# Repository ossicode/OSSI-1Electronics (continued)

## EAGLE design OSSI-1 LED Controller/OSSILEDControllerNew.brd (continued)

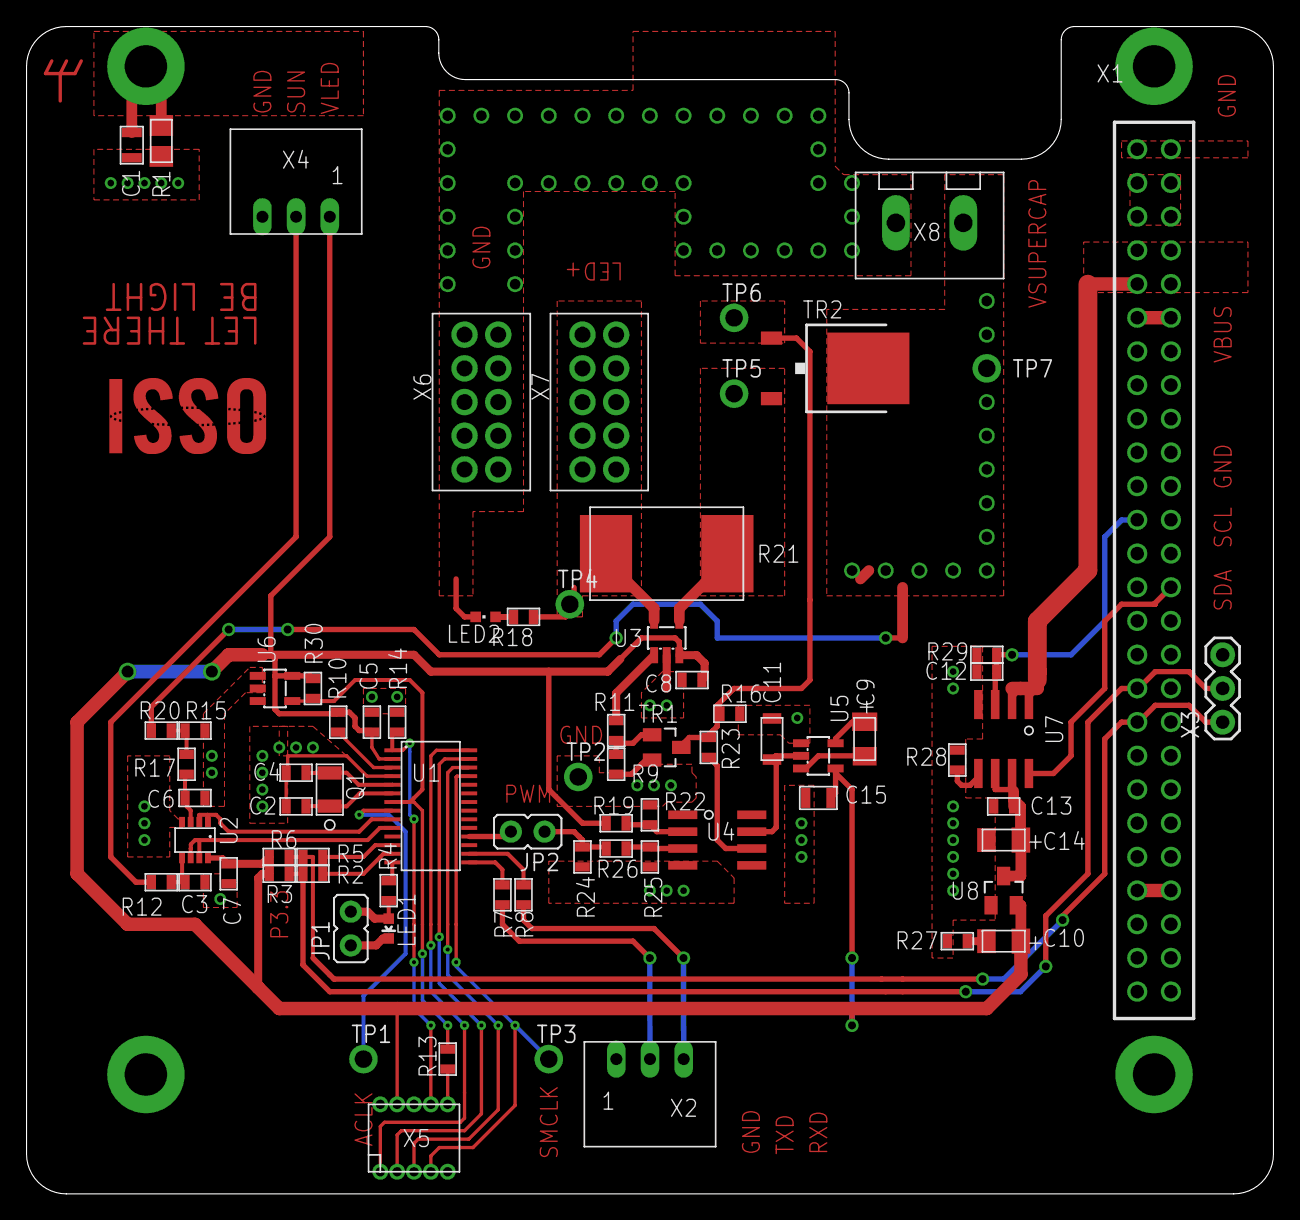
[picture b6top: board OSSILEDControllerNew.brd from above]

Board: 2 copper layers, 94.0 x 88.0 mm, 80 parts (0 on the bottom side), 54 nets.

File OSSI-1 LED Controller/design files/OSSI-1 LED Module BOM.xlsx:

Part | Value | Package | Description | Note | Manufacturer | Part Num | Order
C1 | DNP | C0805(2012)
H1 | MOUNT-PAD-ROUND3.2 | 3.2-PAD-ROUND
H2 | MOUNT-PAD-ROUND3.2 | 3.2-PAD-ROUND
H3 | MOUNT-PAD-ROUND3.2 | 3.2-PAD-ROUND
H4 | MOUNT-PAD-ROUND3.2 | 3.2-PAD-ROUND
R1 | DNP | WSL1206
X1 | ESQ-126-38-G-D | ESQ-126-XX-X-D | Samtec ESQ-126-XX-G-D Elevated Sockets Seires | Used by many satellites | Samtec | ESQ-126-38-G-D | Samtec.com
C2 | 12.5pF | C0603(1608)
C3 | 100nF | C0603(1608)
C4 | 12.5pF | C0603(1608)
C5 | 100nF | C0603(1608)
C6 | 100nF | C0603(1608)
C7 | 100nF | C0603(1608)
C8 | 100nF | C0603(1608)
C9 | 10uF, LDO Tantal 16V | C1206(3216)-A | TAJA105M020RNJ | Tantal Capacitor for LDO | Vishay Sprague | TR3A106K016C1700 | Digikey.com
C10 | 10uF, LDO Tantal 16V | C1206(3216)-A | TAJA105M020RNJ | Tantal Capacitor for LDO | Vishay Sprague | TR3A106K016C1700 | Digikey.com
C11 | 4.7uF, 1206 Cap | C1206-GCM31
C12 | 1uF | C0603(1608)
C13 | 100nF | C0603(1608)
C14 | 10uF, LDO Tantal 16V | C1206(3216)-A | TAJA105M020RNJ | Tantal Capacitor for LDO | Vishay Sprague | TR3A106K016C1700 | Digikey.com
C15 | 1uF 0805 | C0805(2012) |  | 35V, X7R | Murata | GCM21BR7YA105KA55L | Digikey.com
JP1 |  | JP1 | JUMPER
JP2 |  | JP1 | JUMPER
LED1 |  | LED-0603 | LEDs
LED2 |  | CHIPLED_0603 | LED
Q1 | NX-3215 | NX-3215 | NDK 32.768 kHz SMD Crystal | Automotive Grade | NDK | NX3215SA-32.768K-STD-MUS-2 | Digikey.com
R2 | 250 | R0603(1608)
R3 | 10k | R0603(1608)
R4 | 1k | R0603(1608)
R5 | 250 | R0603(1608)
R6 | 10k | R0603(1608)
R7 | 4.7k | R0603(1608)
R8 | 4.7k | R0603(1608)
R9 | 3k | R0603(1608)
R10 | 1k | R0603(1608)
R11 | 5.1k | R0603(1608)
R12 | 1k | R0603(1608)
R13 | 4.7k | R0603(1608)
R14 | 47k | R0603(1608)
R15 | 100k | R0603(1608)
R16 | DNP | R0603(1608)
R17 | 1k | R0603(1608)
R18 | 1.5k | R0603(1608)
R19 | 2.4k | R0603(1608)
R20 | 100k | R0603(1608)
R21 | 0.005, 2W RSENSE | R4527(12070) |  | High Power (2W) 1% Current Sense Resistor | Vishay Dale | WSR25L000FEA | element14.com
R22 | 1.1k | R0603(1608)
R23 | 1k | R0603(1608)
R24 | 100k | R0603(1608)
R25 | DNP | R0603(1608)
R26 | 1.5k | R0603(1608)
R27 | 0 | R0603(1608)
R28 | TBD | R0603(1608)
R29 | 100k | R0603(1608)
R30 | 100k | R0603(1608)
TP1 | TP | TP-13
TP2 | TP | TP-13
TP3 | TP | TP-13
TP4 | TP | TP-13
TP5 | TP | TP-13
TP6 | TP | TP-13
TP7 | TP | TP-13
TR1 | FDV301N | SOT23 | FDV301N Digital N channel - FET | Used sucessfully by swisscube | Fairchild Semiconductor | FDV301N | Digikey.com
TR2 | FDD8896 | TO252 | FDD8896 | 30V 94A N-Ch Mosfet for 9A pulse LED driving | Fairchild Semiconductor | FDD8896 | Digikey.com
U$ | OSSILOGORECT | OSSILOGORECT1005
U1 | MSP430F2132 | PW28 | *** MSP430F21x2 *** PW28 | high current rating | Texas Instruements | MSP430F2132TPWR | Digikey.com
U2 | OPA2347 | SOT23-8DCN | OPA2347 | op-amp | Texas Instruements | OPA2347EA/250 | Digikey.com
U3 | MAX4376 | SOT23-5DBV |  | Current Sensor, Gain = 50 | Maxim IC | MAX4376FAUK+T | Digikey.com
U4 | LM7321 | SO8 | LM7321 | op-amp used as mosfet driver | Texas Instruements | LM7321MA/NOPB | element14.com
U5 | MAX1682 | SOT23-5DBV | MAX1682EUK+T Charge Pump | Charge pump for lm7321 power | Maxim IC | MAX1682EUK+T | Digikey.com
U6 | TPS3838 | SOT23-5DBV | TPS3838 | IC Supervisor for relaible power-on | Texas Instruements | TPS3838K33QDBVRQ1 | Digikey.com
U7 | MAX890L | SO8 | MAX 890L | Current Limiter for SEU / SEL | Maxim IC | MAX890LESA+ | Digikey.com
U8 | MCP1700_SOT23 | SOT23 | MCP1700 LDO from Microchips | LDO used successfully by cubesats / External Capacitor is not that important co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 | Microchip | MCP1700T-3302E/TT | Digikey.com
X2 | 5268-03 | 5268-03
X3 |  | 1X03 | Header 3
X4 | 5268-03 | 5268-03
X5 | JTAG10PINMINI-H | M50-3200545 |  | Mini right angle 10-pin JTAG for MSP430 | Harwin Inc | M50-3200545 | Digikey.com
X6 | ICCON_POWERCON | ICCON6643220-1 |  | 35A rated power connector for led power | TE Connectivity | 6643220-1
X7 | ICCON_POWERCON | ICCON6643220-1 |  | 35A rated power connector for led power | TE Connectivity | 6643220-1
X8 | WEIDMULLER | WEIDMULLER1760490000 |  | 15A rated connector for led connection | Weidmuller | 1760490000
Unless noted othersie,_x000a_- Capacitors: GCM series from Murata / CGA series 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

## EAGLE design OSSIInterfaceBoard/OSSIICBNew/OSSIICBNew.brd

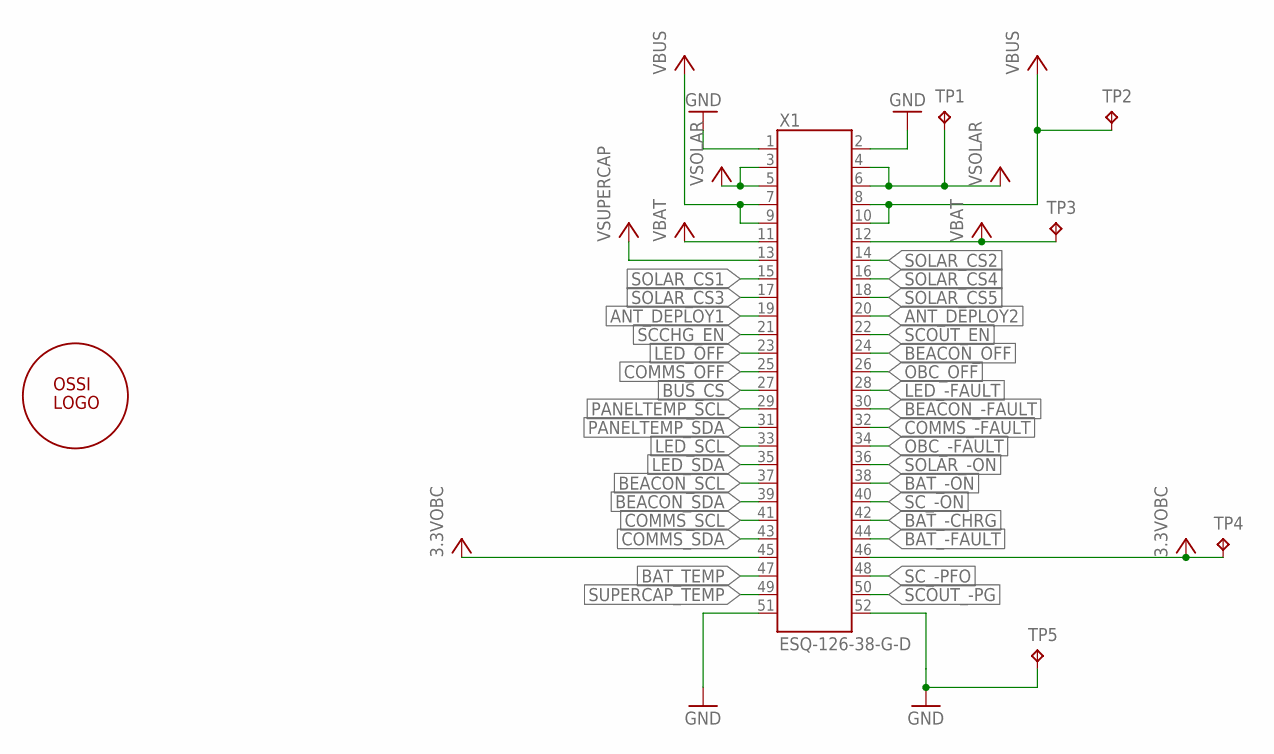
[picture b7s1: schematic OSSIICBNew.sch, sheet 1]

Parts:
TP1, TP2, TP3, TP4, TP5: TP; TP-13
U$1: OSSILOGO-10; OSSILOGO1010
X1: ESQ-126-38-G-D; ESQ-126-XX-X-D

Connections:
3.3VOBC: TP4.TP, X1.45, X1.46; also elsewhere on the board
ANT_DEPLOY1: X1.19
ANT_DEPLOY2: X1.20
BAT_-CHRG: X1.42
BAT_-FAULT: X1.44
BAT_-ON: X1.38
BAT_TEMP: X1.47
BEACON_-FAULT: X1.30
BEACON_OFF: X1.24
BEACON_SCL: X1.37
BEACON_SDA: X1.39
BUS_CS: X1.27
COMMS_-FAULT: X1.32
COMMS_OFF: X1.25
COMMS_SCL: X1.41
COMMS_SDA: X1.43
GND: TP5.TP, X1.1, X1.2, X1.51, X1.52; also elsewhere on the board
LED_-FAULT: X1.28
LED_OFF: X1.23
LED_SCL: X1.33
LED_SDA: X1.35
OBC_-FAULT: X1.34
OBC_OFF: X1.26
PANELTEMP_SCL: X1.29; also elsewhere on the board
PANELTEMP_SDA: X1.31; also elsewhere on the board
SCCHG_EN: X1.21
SCOUT_-PG: X1.50
SCOUT_EN: X1.22
SC_-ON: X1.40
SC_-PFO: X1.48
SOLAR_-ON: X1.36
SOLAR_CS1: X1.15; also elsewhere on the board
SOLAR_CS2: X1.14; also elsewhere on the board
SOLAR_CS3: X1.17; also elsewhere on the board
SOLAR_CS4: X1.16; also elsewhere on the board
SOLAR_CS5: X1.18; also elsewhere on the board
SUPERCAP_TEMP: X1.49
VBAT: TP3.TP, X1.11, X1.12
VBUS: TP2.TP, X1.7, X1.8, X1.9, X1.10
VSOLAR: TP1.TP, X1.3, X1.4, X1.5, X1.6; also elsewhere on the board
VSUPERCAP: X1.13

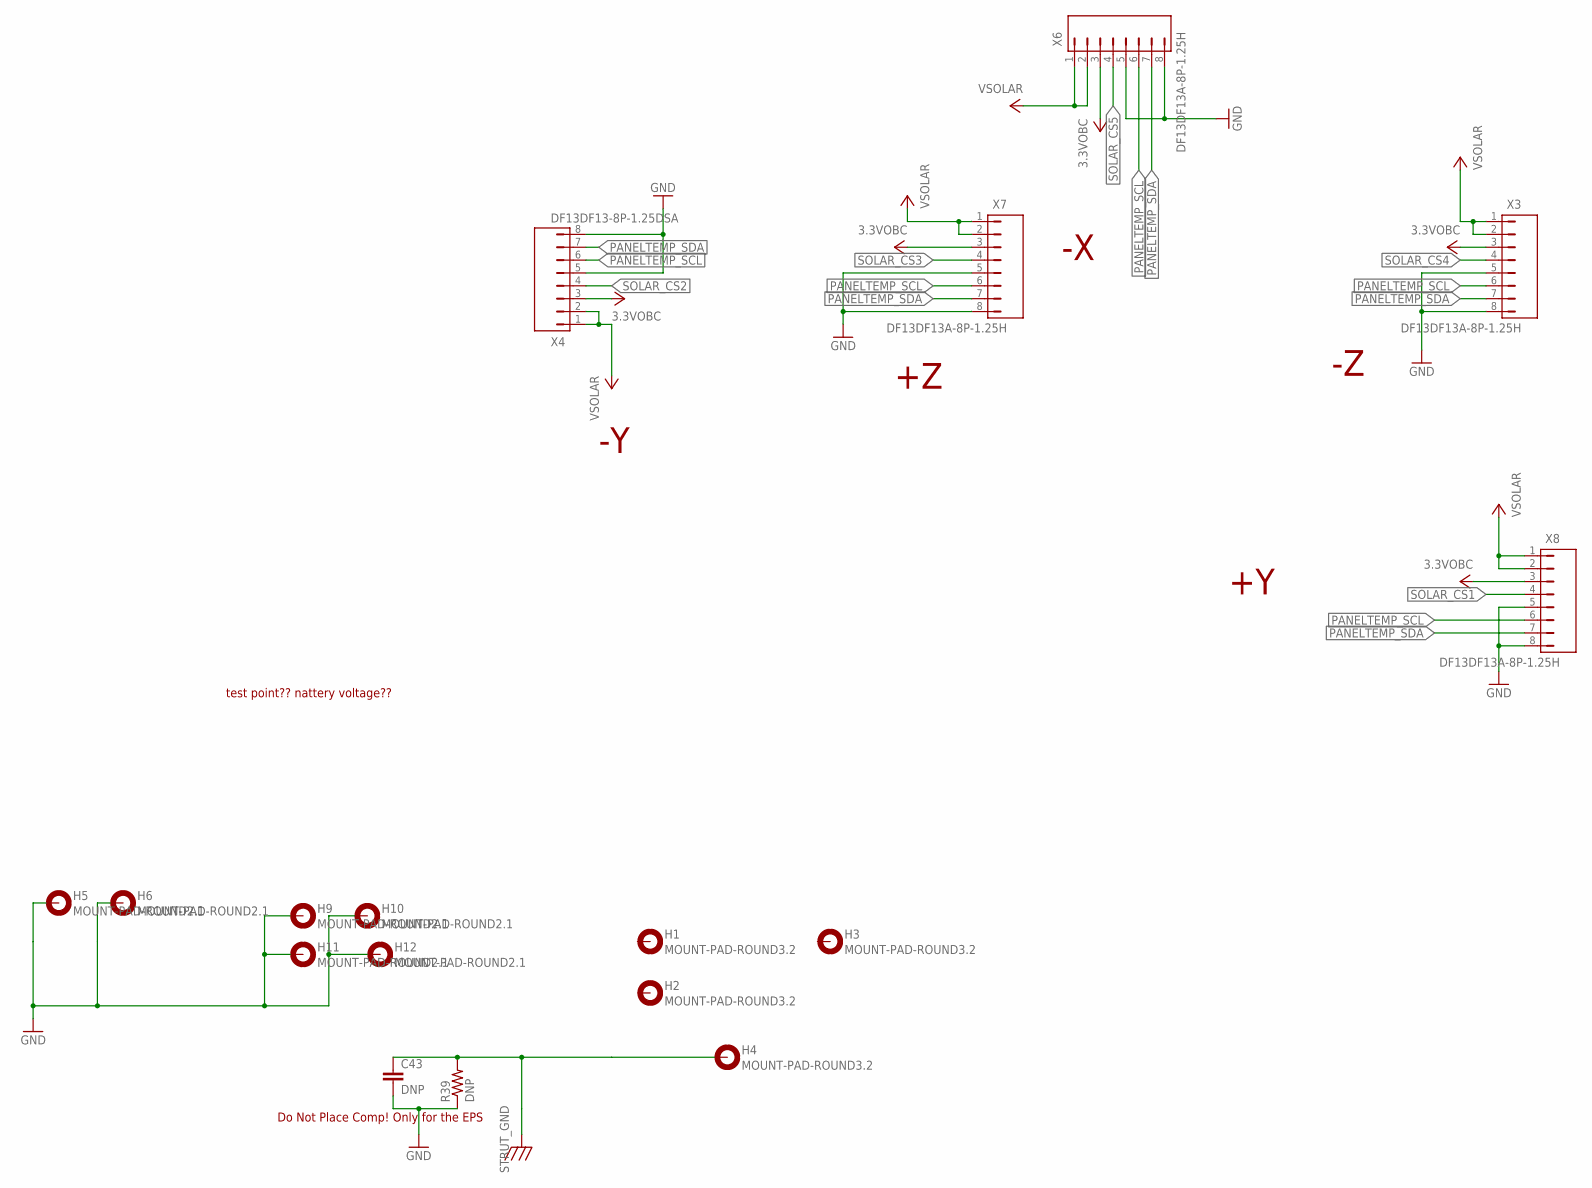
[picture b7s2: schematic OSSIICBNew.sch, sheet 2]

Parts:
C43: DNP; C0805(2012)
H1, H2, H3, H4: MOUNT-PAD-ROUND3.2; 3.2-PAD-ROUND
H5, H6, H9, H10, H11, H12: MOUNT-PAD-ROUND2.1; 2.1-PAD-ROUND
R39: DNP; WSL1206
X3, X6, X7, X8: DF13DF13A-8P-1.25H; DF13A-8P
X4: DF13DF13-8P-1.25DSA; DF13-8P-1.25DSA

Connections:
3.3VOBC: X3.3, X4.3, X6.3, X7.3, X8.3; also elsewhere on the board
GND: C43.2, H5.B3,2, H6.B3,2, H9.B3,2, H10.B3,2, H11.B3,2, H12.B3,2, R39.P$1 (1), X3.5, X3.8, X4.5, X4.8, X6.5, X6.8, X7.5, X7.8, X8.5, X8.8; also elsewhere on the board
PANELTEMP_SCL: X3.6, X4.6, X6.6, X7.6, X8.6; also elsewhere on the board
PANELTEMP_SDA: X3.7, X4.7, X6.7, X7.7, X8.7; also elsewhere on the board
SOLAR_CS1: X8.4; also elsewhere on the board
SOLAR_CS2: X4.4; also elsewhere on the board
SOLAR_CS3: X7.4; also elsewhere on the board
SOLAR_CS4: X3.4; also elsewhere on the board
SOLAR_CS5: X6.4; also elsewhere on the board
STRUT_GND: C43.1, H4.B3,2, R39.P$2 (2)
VSOLAR: X3.1, X3.2, X4.1, X4.2, X6.1, X6.2, X7.1, X7.2, X8.1, X8.2; also elsewhere on the board

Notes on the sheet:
test point?? nattery voltage??
Do Not Place Comp! Only for the EPS

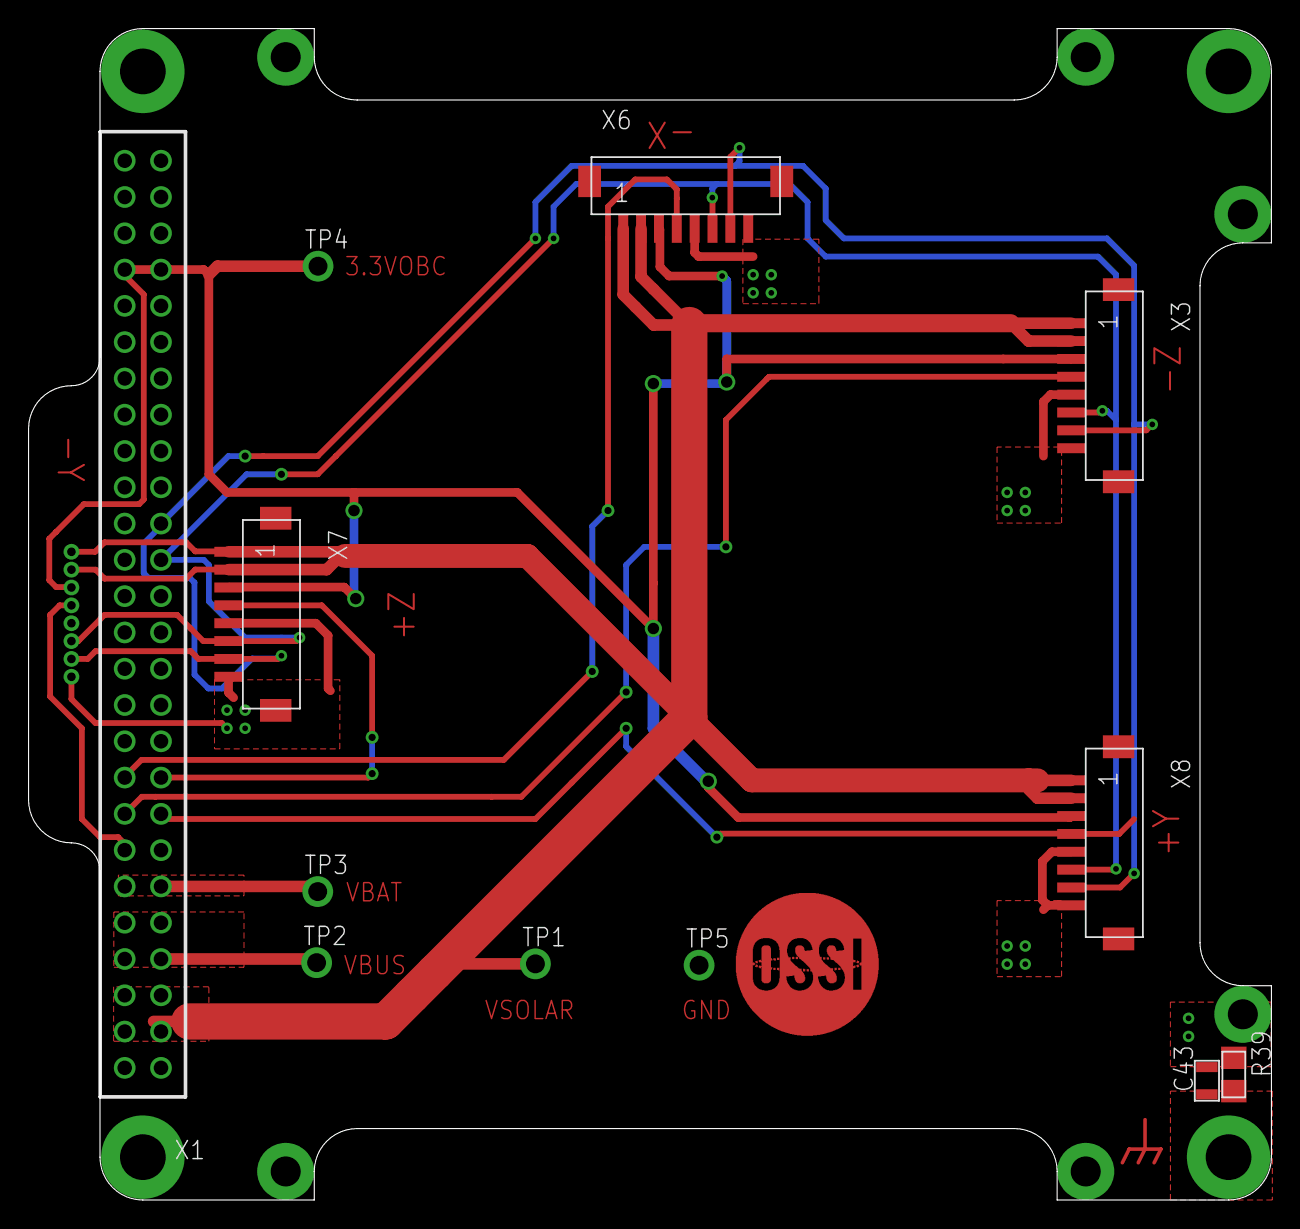
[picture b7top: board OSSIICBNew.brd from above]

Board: 2 copper layers, 87.0 x 82.0 mm, 24 parts (1 on the bottom side), 13 nets.

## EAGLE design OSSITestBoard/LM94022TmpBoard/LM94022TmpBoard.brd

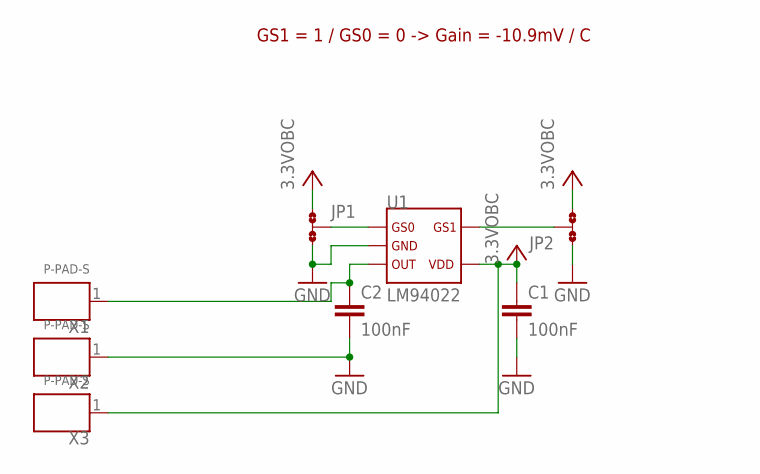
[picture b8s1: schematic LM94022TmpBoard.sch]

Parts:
C1, C2: 100nF; C0603(1608)
JP1, JP2: JP2; JP2SMD0603
U1: LM94022; SC70-5
X1, X2, X3: P-PAD-S

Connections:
3.3VOBC: C1.1, JP1.1, JP2.3, U1.P$4, X3.1
GND: C1.2, C2.2, JP1.3, JP2.1, U1.P$2, X2.1
unnamed: JP1.2, U1.P$1
unnamed: JP2.2, U1.P$5
unnamed: C2.1, U1.P$3, X1.1

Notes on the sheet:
GS1 = 1 / GS0 = 0 -> Gain = -10.9mV / C

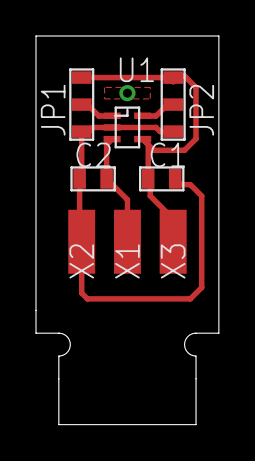
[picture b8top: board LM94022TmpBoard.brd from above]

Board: 2 copper layers, 10.2 x 21.6 mm, 8 parts (0 on the bottom side), 5 nets.

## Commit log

2012-10-20 Readme added
2012-10-20 combining all OSSI-1 electronics related repositories
2012-12-05 LFCSP_VD package for ADL5530 updated
2012-12-05 ADF7012 based OSSI-1 New Beacon Board project created
2012-12-06 MSP430F2132 added / New Beacon Modified
2012-12-06 OSSI New Beacon Board Circuit 90% done
2012-12-06 New Beacon board updating
2012-12-07 CX5032 19.2MHz crystal added to library
2012-12-07 OSSI New Beacon Almost done
2012-12-10 OSSI New Beacon layout done
2012-12-10 I2C Testboard gerber done / New Beacon gerber done
2012-12-21 OSSI COMMS PA components value changed based on Swisscube
2013-01-24 OSSI Shield Library Added
2013-01-24 OSSI Dev Board Alpha added
2013-01-29 EPS comment added to Chassis Structure GND move
2013-01-29 2132 based LED controller being made / related lbr updated
2013-01-29 MCP1700 SO23 added
2013-01-30 Chage EPS StrutGND R size to 1206!!! note added
2013-02-05 New OBC being made
2013-02-06 New OBC schematic / board file ok
2013-02-06 OSSI OBC New Gerber file added
2013-02-07 New OBC / LTC3105 / LM94022 Board gerber added
2013-02-07 +Xpanel size changed
2013-02-10 LTC3105 board notes added
2013-02-12 comment added
2013-02-17 new eps board being added
2013-02-17 eps board almost done
2013-02-18 battery supercap board added / library added
2013-02-18 supercap battery board added
2013-02-18 led controller board almost done
2013-02-19 beacon newnew led new
2013-02-19 series resistor added
2013-02-20 beacon almost done
2013-02-20 gerber files are created / led current setting fixed to 9.7A
2013-02-20 ossi comms new added
2013-02-21 beta 1 release
2013-02-22 schematics renumbered
2013-02-22 LNA gain measured to 15.5dB and R / L values are fixed
2013-02-22 LNA values
2013-02-23 COMMS PA setting fixed!
2013-02-25 beacon valued corrected
2013-02-25 beacon value changed
2013-02-25 comms names renumbred
2013-02-25 led controlloer renumbered
2013-02-25 EPS renumbered
2013-02-25 OBC renumbered
2013-03-04 all values for tuned results are updated
2013-03-04 front panel value
2013-03-29 comms value
2013-07-07 some library description updated
2013-12-30 backup
2014-03-06 Create gh-pages branch via GitHub
2014-03-07 design file are added / missing values are added
2014-03-07 design files are added
2014-03-08 design flies are added
2014-03-08 led sch updated / design files are added
2014-03-08 temp board file added
2014-03-08 got rid of old files
2014-03-08 more cleanup
2014-03-08 size
2014-03-08 minor
2014-03-11 opa347 setting corrected
2014-03-12 sch pdf file added
2014-03-14 image file added
2014-03-15 image added
2014-03-16 sch corrected
2014-03-18 value comment changed
2014-03-18 pdf added
2014-03-18 tuning power cap commet added
    22uF near the adf7021-n is added for better performance by lowering the
    power noised
2014-03-18 excel file added
2014-03-18 bom text file deleted
2014-03-18 excel bom file is added
2014-03-18 excel files are added
